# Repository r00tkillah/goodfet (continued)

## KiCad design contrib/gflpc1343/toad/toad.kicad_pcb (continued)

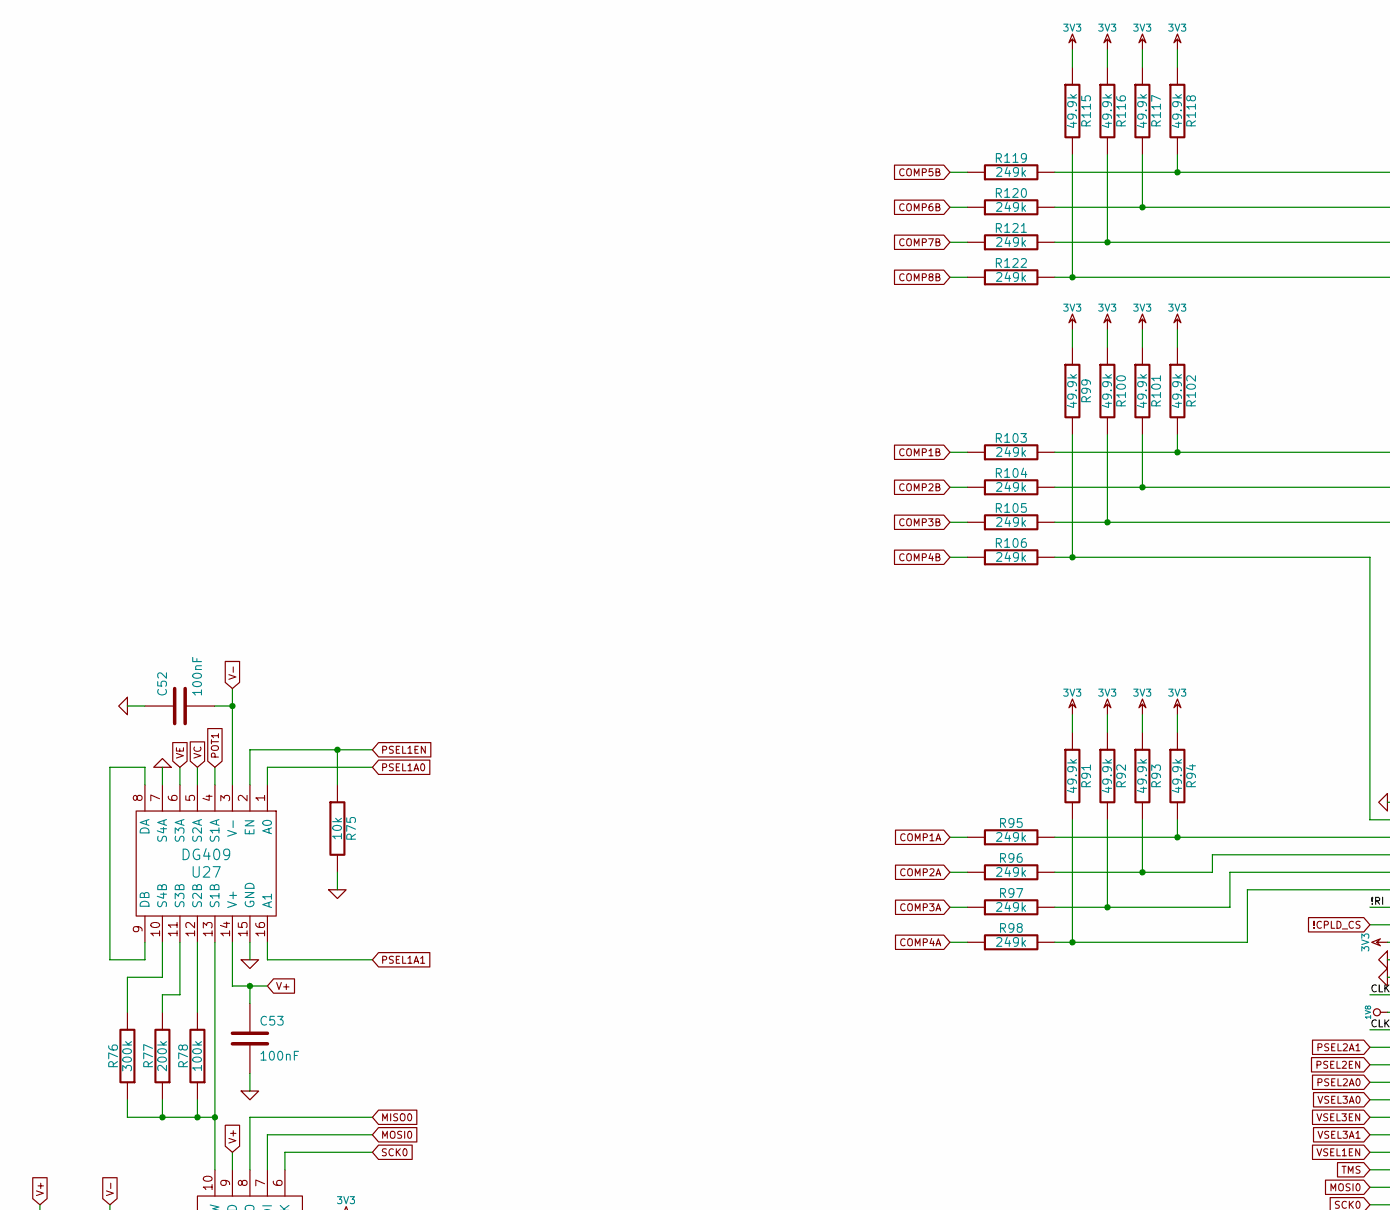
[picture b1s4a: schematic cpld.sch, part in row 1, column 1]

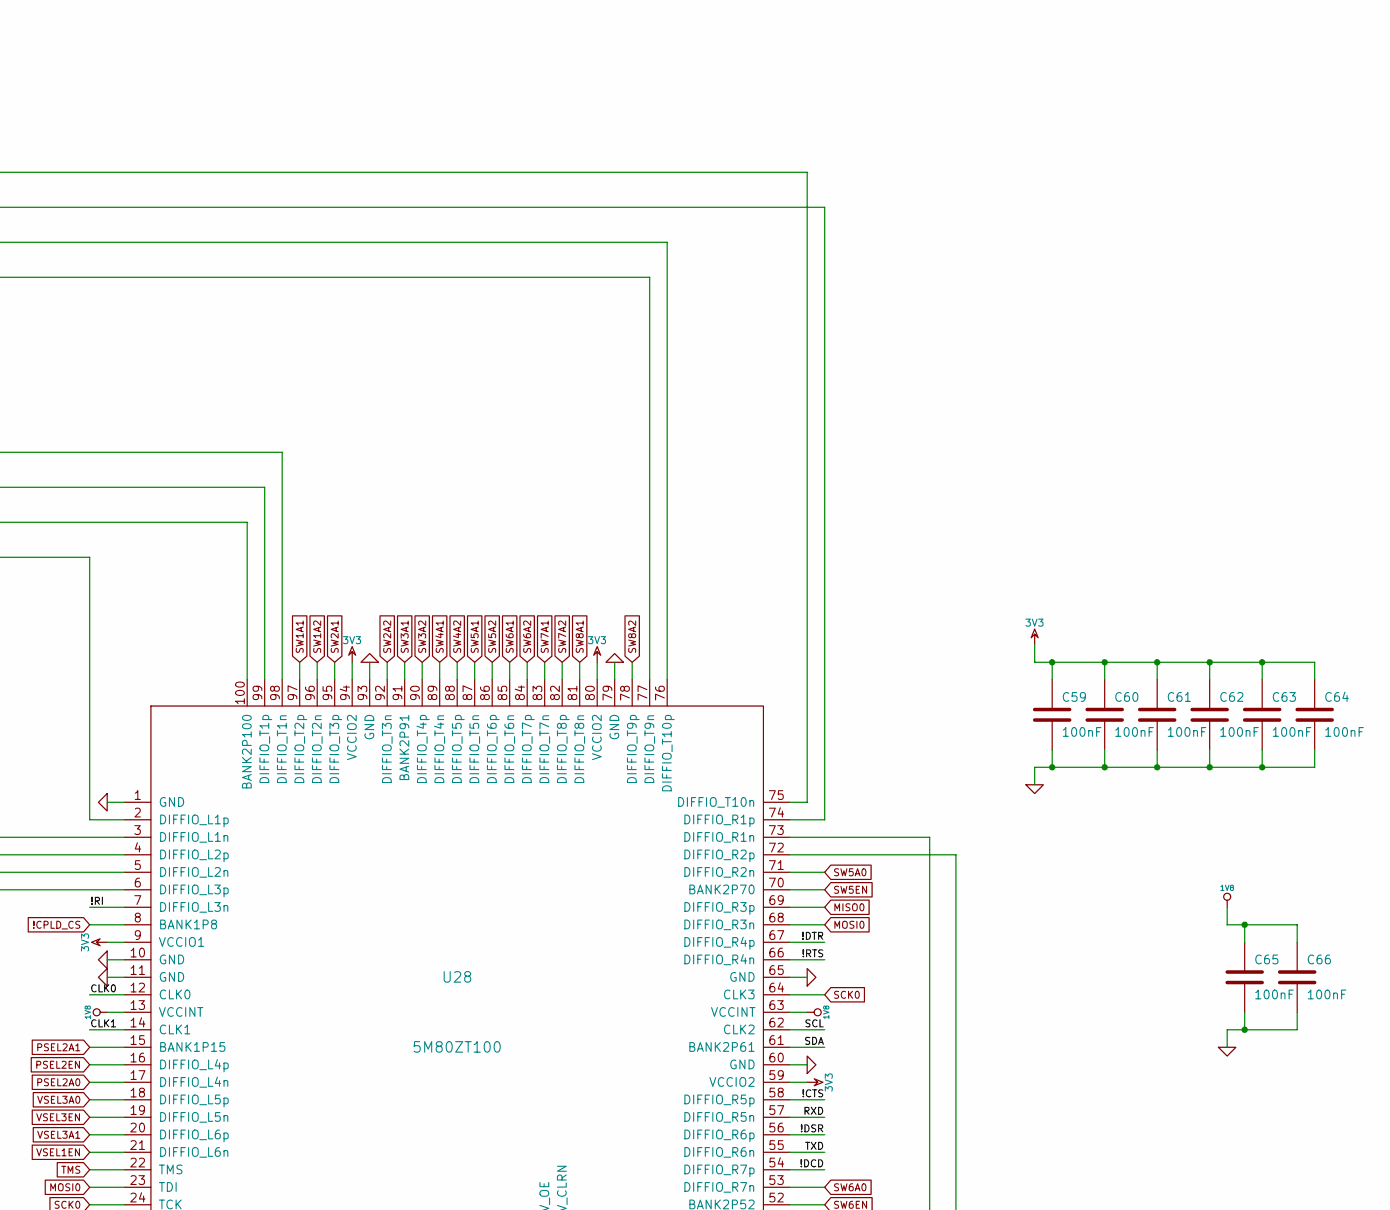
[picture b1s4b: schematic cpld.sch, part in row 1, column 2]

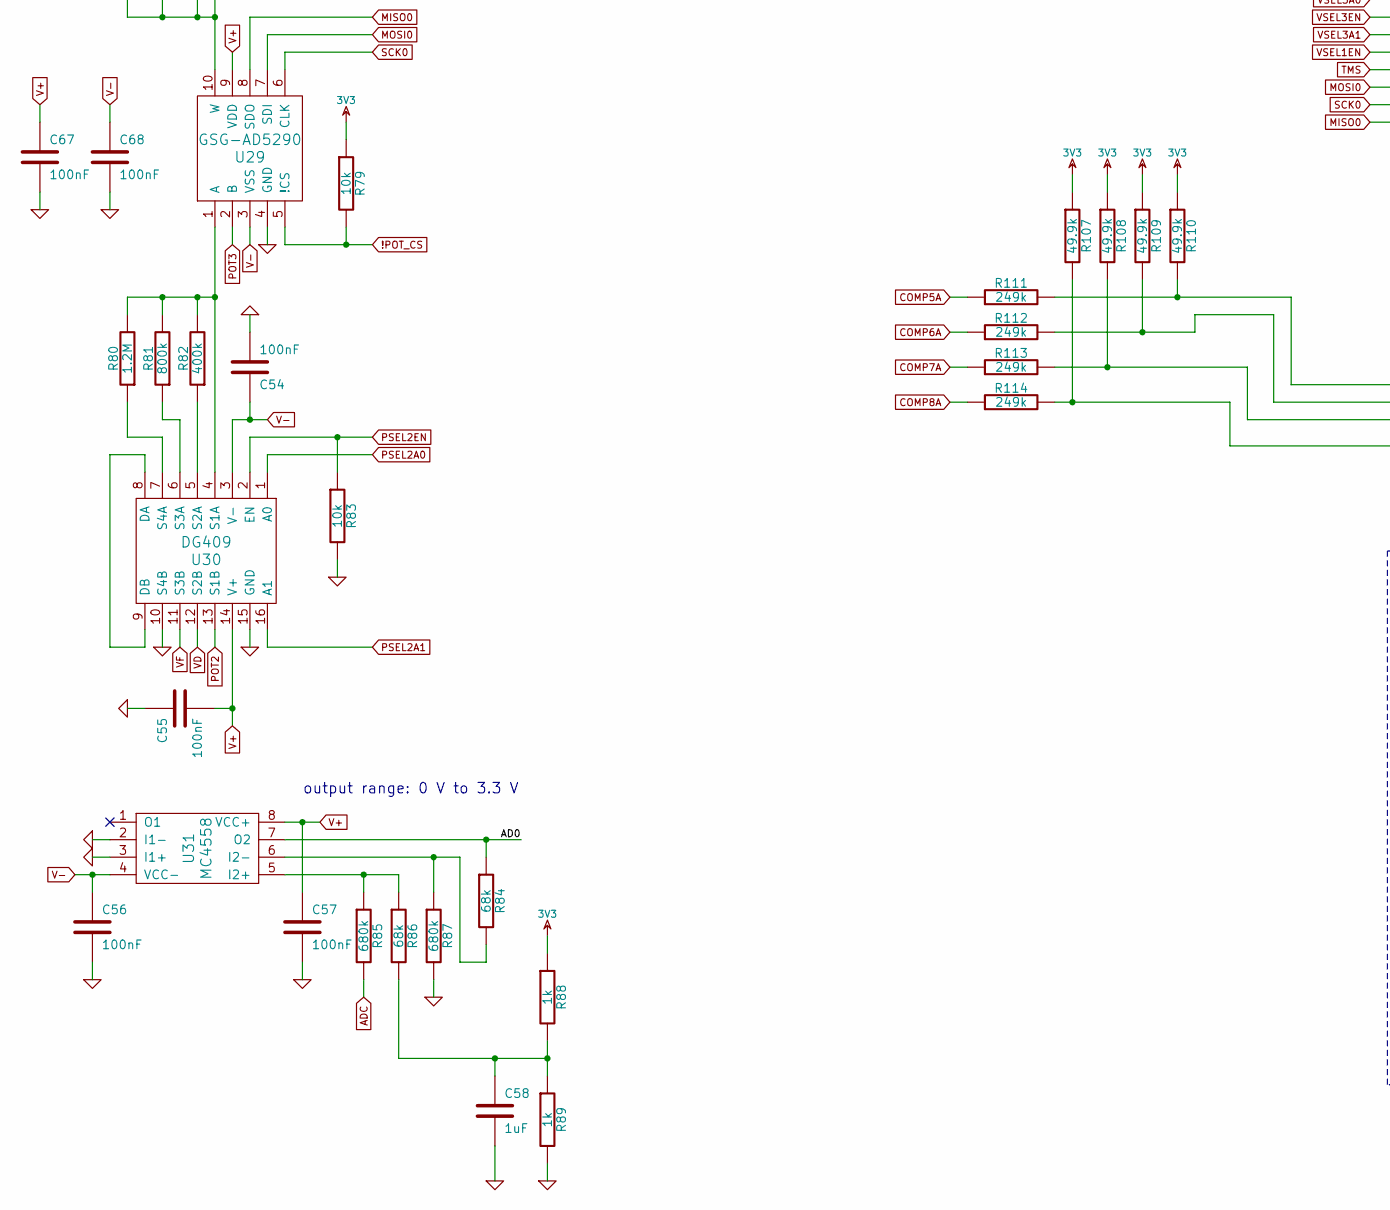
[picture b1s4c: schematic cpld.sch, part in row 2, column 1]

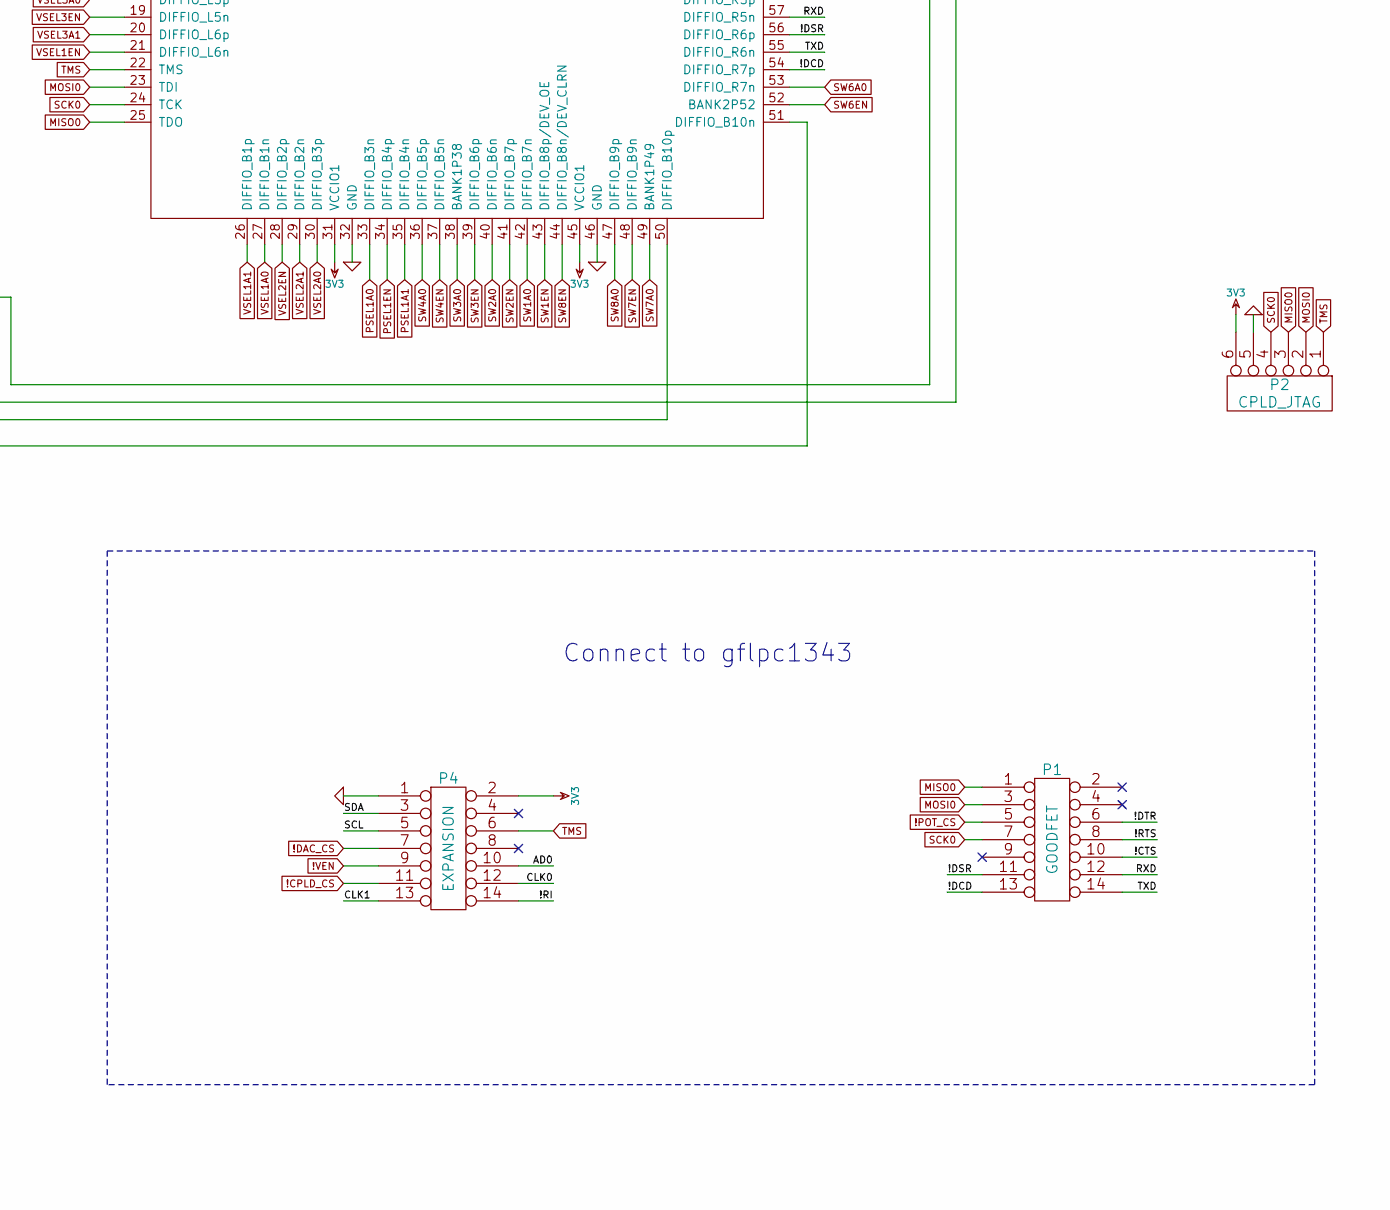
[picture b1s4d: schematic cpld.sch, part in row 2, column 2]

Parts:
C52, C53, C54, C55, C56, C57, C59, C60, C61, C62, C63, C64, C65, C66, C67, C68: 100nF; Part Number CL10B104KB8SFNC
C58: 1uF; Part Number CL10A105KB8NNNC
P1: GOODFET
P2: CPLD_JTAG
P4: EXPANSION
R75, R79, R83: 10k
R76: 300k
R77: 200k
R78: 100k
R80: 1.2M
R81: 800k
R82: 400k
R84, R86: 68k
R85, R87: 680k
R88, R89: 1k
R91, R92, R93, R94, R99, R100, R101, R102, R107, R108, R109, R110, R115, R116, R117, R118: 49.9k
R95, R96, R97, R98, R103, R104, R105, R106, R111, R112, R113, R114, R119, R120, R121, R122: 249k
U27, U30: DG409; Part Number DG409DQ-T1-E3
U28: 5M80ZT100; Part Number 5M80ZT100C5N
U29: GSG-AD5290; Part Number AD5290YRMZ100
U31: MC4558; Part Number MC4558CPT

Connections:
3V3: C59.1, C60.1, C61.1, C62.1, C63.1, C64.1, P2.6, P4.2, R79.1, R88.1, R91.1, R92.1, R93.1, R94.1, R99.1, R100.1, R101.1, R102.1, R107.1, R108.1, R109.1, R110.1, R115.1, R116.1, R117.1, R118.1, U28.9 (VCCIO1), U28.31 (VCCIO1), U28.45 (VCCIO1), U28.59 (VCCIO2), U28.80 (VCCIO2), U28.94 (VCCIO2); also elsewhere on the board
!CPLD_CS: P4.11, U28.8 (BANK1P8)
!POT_CS: P1.5, R79.2, U29.5 (!CS)
!VEN: P4.9; also elsewhere on the board
+1.8V: C65.1, C66.1, U28.13 (VCCINT), U28.63 (VCCINT); also elsewhere on the board
/CPLD, ADC, potentiometer/!CTS: P1.10, U28.58 (DIFFIO_R5p)
/CPLD, ADC, potentiometer/!DCD: P1.13, U28.54 (DIFFIO_R7p)
/CPLD, ADC, potentiometer/!DSR: P1.11, U28.56 (DIFFIO_R6p)
/CPLD, ADC, potentiometer/!DTR: P1.6, U28.67 (DIFFIO_R4p)
/CPLD, ADC, potentiometer/!RI: P4.14, U28.7 (DIFFIO_L3n)
/CPLD, ADC, potentiometer/!RTS: P1.8, U28.66 (DIFFIO_R4n)
/CPLD, ADC, potentiometer/AD0: P4.10, R84.1, U31.7 (O2)
/CPLD, ADC, potentiometer/CLK0: P4.12, U28.12 (CLK0)
/CPLD, ADC, potentiometer/CLK1: P4.13, U28.14 (CLK1)
/CPLD, ADC, potentiometer/RXD: P1.12, U28.57 (DIFFIO_R5n)
/CPLD, ADC, potentiometer/SCL: P4.5, U28.62 (CLK2)
/CPLD, ADC, potentiometer/SDA: P4.3, U28.61 (BANK2P61)
/CPLD, ADC, potentiometer/TXD: P1.14, U28.55 (DIFFIO_R6n)
ADC: R85.2; also elsewhere on the board
COMP1A: R95.1; also elsewhere on the board
COMP1B: R103.1; also elsewhere on the board
COMP2A: R96.1; also elsewhere on the board
COMP2B: R104.1; also elsewhere on the board
COMP3A: R97.1; also elsewhere on the board
COMP3B: R105.1; also elsewhere on the board
COMP4A: R98.1; also elsewhere on the board
COMP4B: R106.1; also elsewhere on the board
COMP5A: R111.1; also elsewhere on the board
COMP5B: R119.1; also elsewhere on the board
COMP6A: R112.1; also elsewhere on the board
COMP6B: R120.1; also elsewhere on the board
COMP7A: R113.1; also elsewhere on the board
COMP7B: R121.1; also elsewhere on the board
COMP8A: R114.1; also elsewhere on the board
COMP8B: R122.1; also elsewhere on the board
MISO0: P1.1, P2.3, U28.25 (TDO), U28.69 (DIFFIO_R3p), U29.8 (SDO)
MOSI0: P1.3, P2.2, U28.23 (TDI), U28.68 (DIFFIO_R3n), U29.7 (SDI); also elsewhere on the board
unnamed: R102.2, R103.2, U28.98 (DIFFIO_T1n)
unnamed: R94.2, R95.2, U28.3 (DIFFIO_L1n)
unnamed: R100.2, R105.2, U28.100 (BANK2P100)
unnamed: R101.2, R104.2, U28.99 (DIFFIO_T1p)
unnamed: R91.2, R98.2, U28.6 (DIFFIO_L3p)
unnamed: R92.2, R97.2, U28.5 (DIFFIO_L2n)
unnamed: R93.2, R96.2, U28.4 (DIFFIO_L2p)
unnamed: R115.2, R122.2, U28.77 (DIFFIO_T9n)
unnamed: R116.2, R121.2, U28.76 (DIFFIO_T10p)
unnamed: R117.2, R120.2, U28.74 (DIFFIO_R1p)
unnamed: R108.2, R113.2, U28.50 (DIFFIO_B10p)
unnamed: R99.2, R106.2, U28.2 (DIFFIO_L1p)
unnamed: R81.1, U30.6 (S3A)
unnamed: R82.1, U30.5 (S2A)
unnamed: R76.1, R77.1, R78.1, U27.13 (S1B), U29.10 (W)
unnamed: R78.2, U27.12 (S2B)
unnamed: R77.2, U27.11 (S3B)
unnamed: R76.2, U27.10 (S4B)
unnamed: U30.8 (DA), U30.9 (DB)
unnamed: U27.8 (DA), U27.9 (DB)
unnamed: R80.2, R81.2, R82.2, U29.1 (A), U30.4 (S1A)
unnamed: R80.1, U30.7 (S4A)
unnamed: R107.2, R114.2, U28.51 (DIFFIO_B10n)
unnamed: R110.2, R111.2, U28.73 (DIFFIO_R1n)
unnamed: R118.2, R119.2, U28.75 (DIFFIO_T10n)
unnamed: R109.2, R112.2, U28.72 (DIFFIO_R2p)
unnamed: C58.1, R86.2, R88.2, R89.1
unnamed: R84.2, R87.1, U31.6 (I2-)
unnamed: R85.1, R86.1, U31.5 (I2+)
POT1: U27.4 (S1A); also elsewhere on the board
POT2: U30.13 (S1B); also elsewhere on the board
POT3: U29.2 (B); also elsewhere on the board
PSEL1A0: U27.1 (A0), U28.33 (DIFFIO_B3n)
PSEL1A1: U27.16 (A1), U28.35 (DIFFIO_B4n)
PSEL1EN: R75.1, U27.2 (EN), U28.34 (DIFFIO_B4p)
PSEL2A0: U28.17 (DIFFIO_L4n), U30.1 (A0)
PSEL2A1: U28.15 (BANK1P15), U30.16 (A1)
PSEL2EN: R83.1, U28.16 (DIFFIO_L4p), U30.2 (EN)
SCK0: P1.7, P2.4, U28.24 (TCK), U28.64 (CLK3), U29.6 (CLK); also elsewhere on the board
SW1A0: U28.42 (DIFFIO_B7n); also elsewhere on the board
SW1A1: U28.97 (DIFFIO_T2p); also elsewhere on the board
SW1A2: U28.96 (DIFFIO_T2n); also elsewhere on the board
SW1EN: U28.43 (DIFFIO_B8p/DEV_OE); also elsewhere on the board
SW2A0: U28.40 (DIFFIO_B6n); also elsewhere on the board
SW2A1: U28.95 (DIFFIO_T3p); also elsewhere on the board
SW2A2: U28.92 (DIFFIO_T3n); also elsewhere on the board
SW2EN: U28.41 (DIFFIO_B7p); also elsewhere on the board
SW3A0: U28.38 (BANK1P38); also elsewhere on the board
SW3A1: U28.91 (BANK2P91); also elsewhere on the board
SW3A2: U28.90 (DIFFIO_T4p); also elsewhere on the board
SW3EN: U28.39 (DIFFIO_B6p); also elsewhere on the board
SW4A0: U28.36 (DIFFIO_B5p); also elsewhere on the board
SW4A1: U28.89 (DIFFIO_T4n); also elsewhere on the board
SW4A2: U28.88 (DIFFIO_T5p); also elsewhere on the board
SW4EN: U28.37 (DIFFIO_B5n); also elsewhere on the board
SW5A0: U28.71 (DIFFIO_R2n); also elsewhere on the board
SW5A1: U28.87 (DIFFIO_T5n); also elsewhere on the board
SW5A2: U28.86 (DIFFIO_T6p); also elsewhere on the board
SW5EN: U28.70 (BANK2P70); also elsewhere on the board
SW6A0: U28.53 (DIFFIO_R7n); also elsewhere on the board
SW6A1: U28.85 (DIFFIO_T6n); also elsewhere on the board
SW6A2: U28.84 (DIFFIO_T7p); also elsewhere on the board
SW6EN: U28.52 (BANK2P52); also elsewhere on the board
SW7A0: U28.49 (BANK1P49); also elsewhere on the board
SW7A1: U28.83 (DIFFIO_T7n); also elsewhere on the board
SW7A2: U28.82 (DIFFIO_T8p); also elsewhere on the board
SW7EN: U28.48 (DIFFIO_B9n); also elsewhere on the board
SW8A0: U28.47 (DIFFIO_B9p); also elsewhere on the board
SW8A1: U28.81 (DIFFIO_T8n); also elsewhere on the board
SW8A2: U28.78 (DIFFIO_T9p); also elsewhere on the board
SW8EN: U28.44 (DIFFIO_B8n/DEV_CLRN); also elsewhere on the board
TMS: P2.1, P4.6, U28.22 (TMS)
VC: U27.5 (S2A); also elsewhere on the board
VD: U30.12 (S2B); also elsewhere on the board
VE: U27.6 (S3A); also elsewhere on the board
VF: U30.11 (S3B); also elsewhere on the board
VSEL1A0: U28.27 (DIFFIO_B1n); also elsewhere on the board
VSEL1A1: U28.26 (DIFFIO_B1p); also elsewhere on the board
VSEL1EN: U28.21 (DIFFIO_L6n); also elsewhere on the board
VSEL2A0: U28.30 (DIFFIO_B3p); also elsewhere on the board
VSEL2A1: U28.29 (DIFFIO_B2n); also elsewhere on the board
VSEL2EN: U28.28 (DIFFIO_B2p); also elsewhere on the board
VSEL3A0: U28.18 (DIFFIO_L5p); also elsewhere on the board
VSEL3A1: U28.20 (DIFFIO_L6p); also elsewhere on the board
VSEL3EN: U28.19 (DIFFIO_L5n); also elsewhere on the board

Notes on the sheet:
output range: 0 V to 3.3 V
Connect to gflpc1343

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
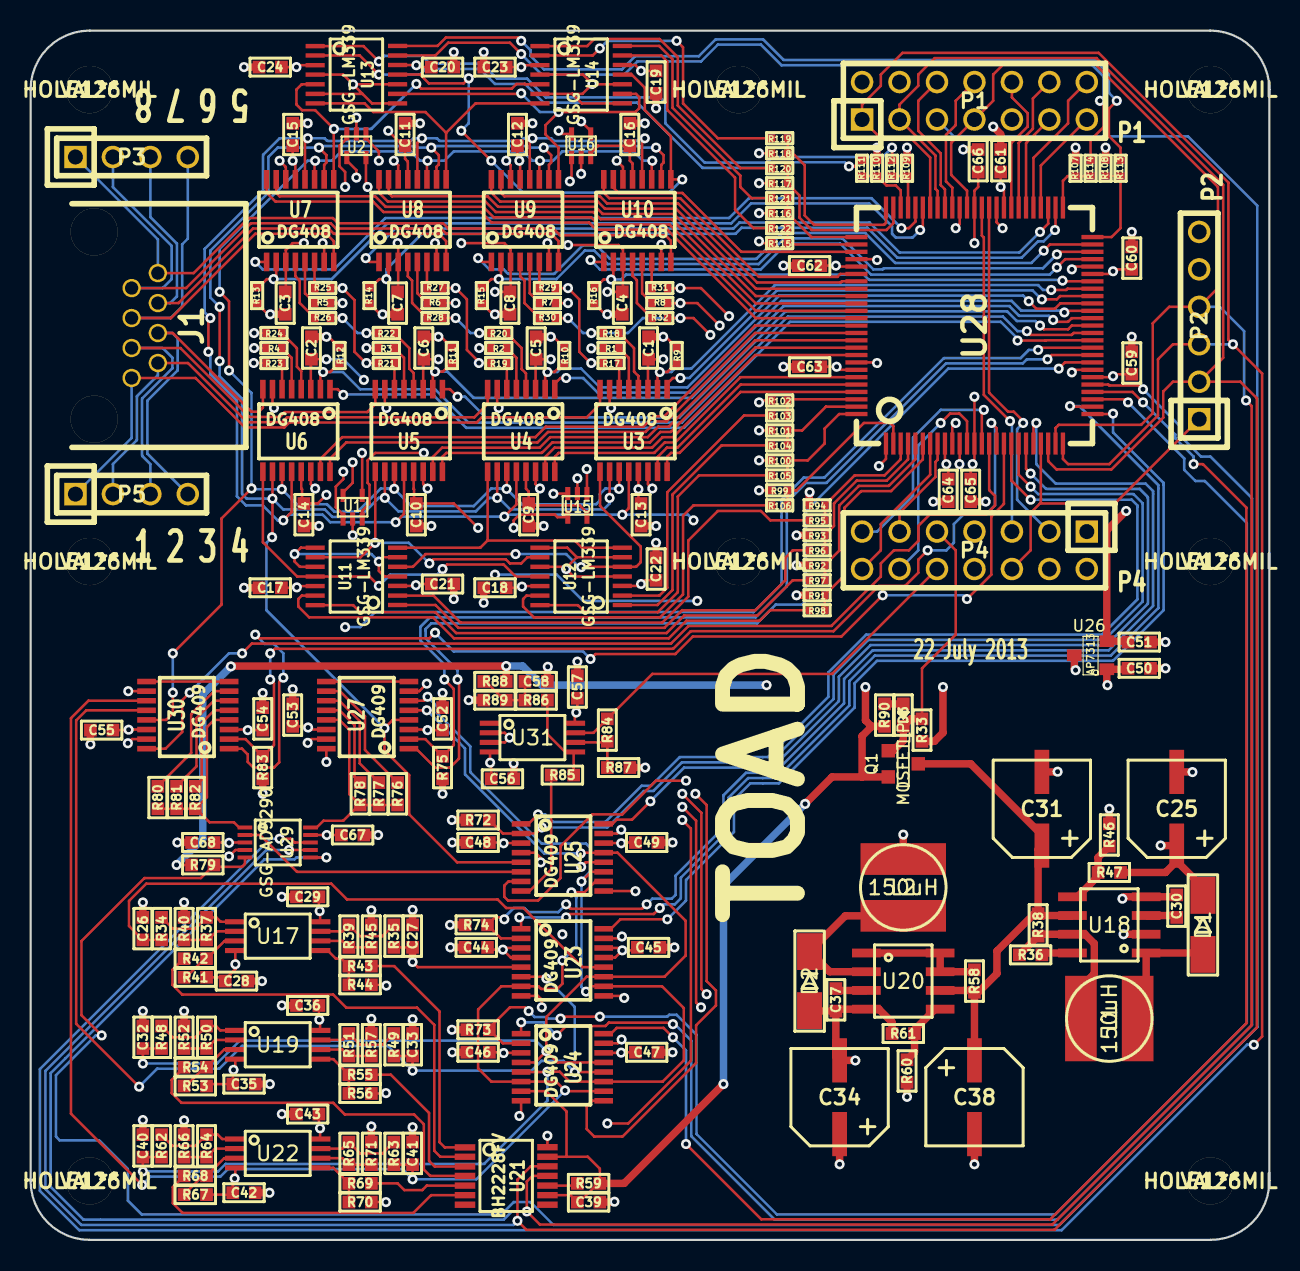
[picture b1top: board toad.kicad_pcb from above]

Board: 4 copper layers, 84.0 x 82.0 mm, 241 parts (0 on the bottom side), 225 nets.

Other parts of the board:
HOLE126MIL, HOLE126MIL#2, HOLE126MIL#3, HOLE126MIL#4, HOLE126MIL#5, HOLE126MIL#6, HOLE126MIL#7, HOLE126MIL#8: VAL**; GSG-HOLE126MIL

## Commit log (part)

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2012-10-01 Minor cleanup.
2012-10-07 Added godfet.maxusbdfu for USD Device Firmware Update emulation with the Facedancer.
2012-10-10 Updated GoodThopter11 Board
2012-10-22 Moved via away from IC in GT11.
2012-10-25 GoodFET42 layout. Might not be final.
2012-10-26 link to example Digi-Key order for Facedancer11 parts
2012-10-30 New code for setting the rate. Tested at 125kHz.
2012-10-30 goodfet.mcpcan's sniff verb now supports setting a data rate.
2012-10-30 Allowing a rate of 83.3
2012-10-31 Created intelligent sniffer (isniff) to help decode CAN messages
2012-11-03 Added GT11, fixed BOM of GT10.
2012-11-03 MCP CAN doccos.
2012-11-03 GT11 firmware.
2012-11-03 Typo.
2012-11-04 Rebuild CAM files for GF42.
2012-11-05 Added win32 instructions.
2012-11-06 Tiny silkscreen placement change in GF42.
2012-11-07 gflpc1343 parts selection, paste clearance
2012-11-07 add Linked List files i forgot
2012-11-09 JTAGARM7 is back up and running, folks! Tested Halt/Release, Get/Set Registers, Read/Write Memory.
2012-11-11 and the peek does the size better (without specifying an end, it was giving odd results)
2012-11-12 updates to use the ARMresettarget() for "goodfet.arm7 reset" which uses the nRST pin
2012-11-15 ARMread/writeStream() functions enabled, allowing the reading/writing of byte-aligned bytes, not just 32-bit word-aligned numbers
2012-11-15 yield instead of returning a list of values for ARMreadChunk. also, check out ARMreadStream and ARMwriteStream functions! way handy for dealing with strings and when you want to be byte-aligned, not 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
2012-11-16 Socks with hops.
2012-11-19 HID patches and a bit of host fingerprinting from Kenny at Romhat.
2012-11-22 goodfet.maxusbmass now has increased to 128 blocks per transfer, fixed failure codes.
2012-11-22 Updated GoodThopter11 HTML page to explain OBD2 cable choice.
2012-11-23 Facedancer20 gerbers.
2012-11-24 Added APP number to GoodFETSPI.
2012-11-25 Beginnings of support for Zigduino. AVR code is really out of shape.
2012-11-30 Status page update. Still needs a rewrite.
2012-12-04 OpenSCAD models for Makerbot-able GoodFET casings.
2012-12-05 OpenSCAD models for the GoodThopter. Parametrics are cool.
2012-12-12 Removed outdated installation instructions.
2012-12-14 Added basic firmware and client support for the zigduino/atmel128rfa1. It can now rx and tx packets.
2013-01-04 Fixed GF42 links. Boards should arrive soon.
2013-01-04 Link to second Facedancer article. Third one ought to be up before too damned much time has passed.
2013-01-04 working on goodfet.bsl improvements to --fromweb and trying to preserve info flash
2013-01-06 This seems to fix the undesired chip erase when doing --dumpinfo
2013-01-15 upload goodfet.mcpcanCommunication.py
2013-01-16 updated DataManage.py with .pcap writing capabilities
2013-01-16 Renaming FD21 files.
2013-01-16 updated DataManage.py
2013-01-17 FD20 erratum, orders.
2013-01-17 FD21 docs.
2013-01-17 FD20 image.
2013-01-17 Added erratum note to FD20 schematic.
2013-01-17 uploaded some data files and reviced Data code
2013-01-20 Two typos in the website.
2013-01-20 Cleaned up tab inconsistency in usb_max.py.
2013-01-22 Updates to GoodFETMCPCANCommunication.py. Pared down SPI transmission in sniff, speeding it up, and added filtering options to filter for packets with specified standard IDs
2013-01-22 updated working GUI file: mainDisplay.py. This should now have working sniff with filtering ability. You can also run a SQL query and save to csv file
2013-01-22 Changes to GoodFETMCPCANCommunication.py. Added file management capabilities back. fixed error
2013-01-23 First draft of GoodFET32.
2013-01-24 testing commit ability
2013-01-24 jtagarm7 interface improvements, including at91x40
2013-01-24 jtagarm7 more obligatory stupid bug fixes, doh!
2013-01-25 added fast packet sniffing option -x. doubles RX speed but could easily result in duplicate packets. use with caution-- should be set to respond to interrupt from MCP
2013-01-25 jtagarm7 at91x40 ecdump updates and bugfixes
2013-01-25 new test file for sweeping
2013-01-26 small changes to upload method in DataManage
2013-01-27 minor updates to spit-testing function
2013-01-29 added parsing abilities to sniff as well as improvements to the simpleGUI
2013-01-29 functionality changes to mainDisplay. added settings, writing section, reorganized and cleaned filtering and sniffing
2013-01-30 GUI updated to include writing and experiment capabilities. Updated spit capabilities to allow for user to set the packet they wish to send
2013-01-30 bug fixes in mainDisplay and spit method of GoodFETMCPCANCommunication
2013-01-30 fixed filtering issue on mainDisplay.py
2013-02-01 spit changes to allow user to run from commandline
2013-02-01 built a rtr sweep to check all ids on the car
2013-02-01 changes to the rtr sweep method in communication file
2013-02-01 changes to communication and sweep methods
2013-02-02 changed the preset values for the experiments
2013-02-03 building arbID information secion in mainDisplay file
2013-02-05 update to threading of sniff on mainDisplay as well as added option to sniff in communication file
2013-02-05 small changes to display
2013-02-05 oops. fix for GoodFETARM9
2013-02-05 jtagarm9 - will get things settled eventually
2013-02-05 changes to get the threading working for sniff in mainDisplay. removed bugs
2013-02-06 changes to the hyperlink commands to allow for arbID link binding
2013-02-06 DataManage to update to Wireshark from SQL
2013-02-06 changes to allow for deltaT of each packet to work. debugged and displaying nicely
2013-02-07 jtagarm: jtag_trans_many tested and working. this will allow us to abstract out all versions of ARM debug interface including ARM7TDMI (existing in gf already), ARM9TDMI, ARM11, ADIv4 and ADIv5 (and 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
2013-02-08 improved ecdump... actually goes back and rereads sections that have failed. failures were causing breaks in segments.
2013-02-11 changes to the display of data
2013-02-11 Somehow the manual.html page wasn't committed to subversion. Here it is.
2013-02-11 More broken images.
2013-02-12 changes to the GUI to allow for better loading and writing as well as tested our FordExperiments stuff
2013-02-12 changes to debug the spit/write code and my ford experiments
2013-02-12 Fix missing links for apps and clients
2013-02-13 minor bug fix on parsing experiments data
2013-02-13 GoodFET32 heading off to the factory.
2013-02-13 updated features for two different types of sniffing. fixed and scrolling. This can be changed on the gui
2013-02-13 added an display for the time difference between every successive packet read off the chip
2013-02-13 Facedancer21 locked in. Ordering soon.
2013-02-14 added packet fuzzing
2013-02-14 Fixed USB host bugs.
2013-02-15 Added the option to automatically re-inject packets that we have fuzzed and injected before. Also added threading to the experiments so that you can set up for the next one while one is running
2013-02-15 generalized the generation fuzzer to allow you to choose which ids you want to randomly inject also
2013-02-18 I2C master app and client. Impressively ugly. Might work occasionally.
2013-02-18 added Comments to a lot of the methods
2013-02-19 updated some new experiment methods. you can now fuzz on all ids randomly as well as do a listen response method
2013-02-19 Added a lot of comments to fully describe alot of the methods we have created.
2013-02-20 added filtering on data bytes; use -db0 and -db1 flag on sniff
2013-02-20 added flexible packet sending function, multiPacketSpit
2013-02-20 debugged my attempt to fake the VIN
2013-02-20 i2c.c fixes including: - timing cleanup - release bus after transactions so other masters may take the bus
2013-02-21 updated the GUI to be more usable. added some error checking, warning dialogs
2013-02-22 added comments, rearranged code to be more readable
2013-02-24 added car module section
2013-02-24 build out demonstration gui
2013-02-24 debugging changes
2013-02-25 Completed packet information display
2013-02-25 debugged speedometer hack, added RPM hack
2013-02-26 added demonstration code
2013-02-26 building demonstration frame
2013-02-26 updates to demonstration display
2013-02-27 added demonstration features
2013-02-27 added information about ids
2013-02-28 beethoven hack
2013-02-28 added diagnostic method
2013-02-28 debugged the demonstration methods
2013-03-01 changes to dbugging
2013-03-06 Website update that was accidentally done from the old URL.
2013-03-13 Developer URL.
2013-03-29 Bug fixes and new features added to zigduino firmware and client. New features include: - auto checksum support added - auto checksum can be enabled and diabled - support for radio's extended operati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
2013-03-30 Releasing GoodThopter12 (requires review) fixing PlugBug, supports multiple OBD2 cables.
2013-04-07 Renamed some LEDs. Closer to ordering GoodThopter12 boards.
2013-04-07 Updated GoodThopter12 HTML page, not linked to menu NEEDS to be pushed.
2013-04-07 Final fixes for GT12. Gerbers coming in the next commit.
2013-04-16 Applying some good recommendations from Bruce Barnett - Add --dumpinfo to --help output - Display usage information before considering board definition - Look at alternatives to curl if it is not ava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
2013-04-17 Moving older bootstrap loader aside in preparation for merging in a newer branched version.
2013-04-17 Documentation updates to reflect changes in --fromweb functionality.
2013-04-24 Provide a little bit more user feedback when serInit is stalling out.
2013-05-04 FD21 and assembled board ordering info.
2013-05-05 GF32 support in the new goodfet.bsl.
2013-05-06 raspdancer11 board: more room around IC and other small changes
2013-05-07 Add raspdancer21 sch & brd
2013-05-09 raspdancer21: fix silkscreen
2013-05-12 raspdancer: larger wires & vias & some tunings
2013-06-04 Added initial support for board=apimote2
2013-06-14 new maxusb library
2013-06-15 Python 3.2 for the rewritten Facedancer clients.
2013-06-16 added documentation
2013-06-19 removing an unecessary failed experiment
2013-06-19 handle scsi mode sense to get umass working under linux
2013-06-19 add (hopefully) support for vendors
2013-06-19 correct ftdi vendor info
2013-06-19 fix endianness in device descriptor
2013-06-21 updating SVN link in tutorial
2013-06-21 removed MySQLdb package necessity
2013-07-13 Fixed merge conflict noticed by @Marsmensch.
2013-07-13 GF32 photo.
2013-07-14 TOAD: CPLD decoupling caps, rearranged headers to expose JTAG, etc.
2013-07-18 TOAD: comparator voltage dividers
2013-08-06 No Such Badge
2013-08-14 Added ordering links for GF42 and FD21 to the FAQ.
2013-08-30 bug fixes from Adam Stasiak <palesius@gmail.com>
2013-08-31 Facedancer support for emulating USB LCD devices.
2013-09-15 44con badge.
2013-09-15 Indentation fixes.
    * stop using TAB's for indentation, some (arguably silly) editors use
    4-space TAB's in Python mode
    * fixed inconsistent indentations
2013-09-15 Add missing newline in trace.
    This error somehow demonstrate the usefulness of "print >>sys.stderr" :)
2013-09-15 Add traces in some conditional blocs that did not have one.
    Easier to make sure of the exact code path used.
2013-09-16 Patches I2C client to dump eeproms + add bus scanning capability (untested yet!!)
2013-09-25 Bad link in I2C website.
2013-09-26 Do not hardcode app_num 0 in GoodFETMonitorApp.
2013-09-26 Factorize serial port opening in GoodFETSerialPort().
2013-10-04 H2HC 2013 Badge, based on gflpc1343
2013-10-26 TOAD layout that I forgot to commit previously
2013-10-27 Preliminary BOM. Not yet tested working.
2013-11-05 No changes to the layout have been made in this file. I just opened the manually edited file from the previous checkin, then saved it without making any changes. The garbage collector removed the unu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
2014-01-03 FD21 mistakenly mentioned errata. Fix from Protagonist.
2014-01-14 change hardcoded port name to use GOODFET env var or default it to /dev/ttyUSB0
2014-02-06 Add support for Zen-Sys ASICs firmware manipulation
2014-03-04 GoodThopter12.
2014-03-16 Fixed URL in the download page.
2014-04-21 It doesn't exactly work. Fixed one error to find another
    $ ./facedancer-skel.py
    Facedancer reset
    GoodFET monitor initialized
    MAXUSB initialized
    MAXUSB enabled
    MAXUSB revision 19
2014-04-25 splat with A
2014-05-17 tested progress from exploit workshop, then untested stuff
    a stupid git does not commit to git enough
2014-05-23 make things a little neater
